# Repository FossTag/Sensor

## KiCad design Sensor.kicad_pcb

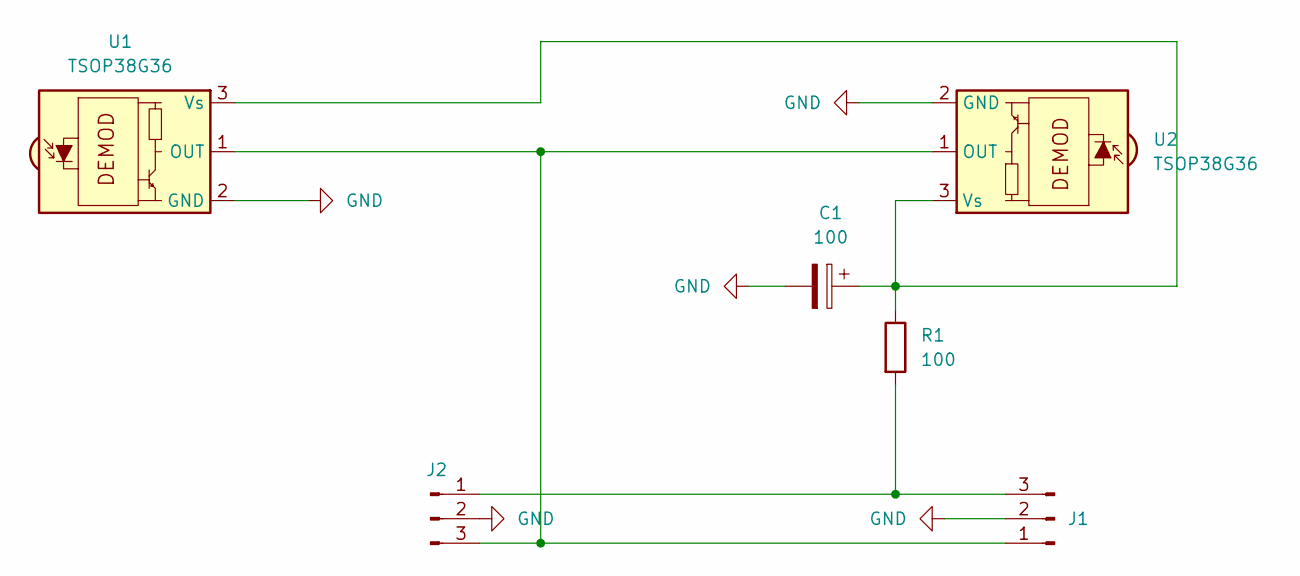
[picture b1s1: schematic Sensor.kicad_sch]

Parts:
C1: 100; CP_Radial_D5.0mm_P2.50mm
J1, J2: Conn_01x03_Male; SolderWire-0.1sqmm_1x03_P3.6mm_D0.4mm_OD1mm_Relief
R1: 100; R_Axial_DIN0204_L3.6mm_D1.6mm_P7.62mm_Horizontal
U1, U2: TSOP38G36; Vishay_MINICAST-3Pin

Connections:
GND: C1.2, J1.2, J2.2, U1.2 (GND), U2.2 (GND)
unnamed: C1.1, R1.1, U1.3 (Vs), U2.3 (Vs)
unnamed: J1.1, J2.3, U1.1 (OUT), U2.1 (OUT)
unnamed: J1.3, J2.1, R1.2

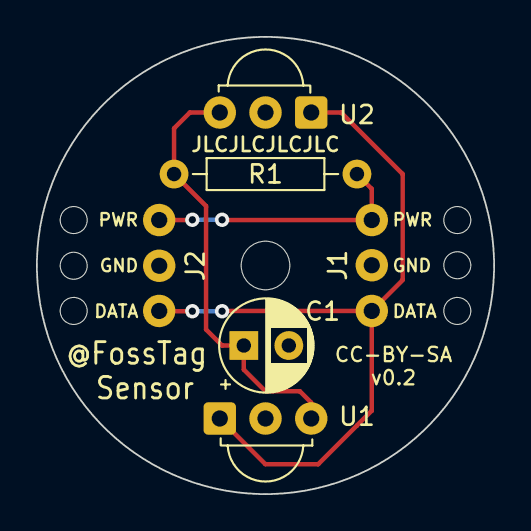
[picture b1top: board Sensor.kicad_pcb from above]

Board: 2 copper layers, 25.4 x 25.4 mm, 6 parts (0 on the bottom side), 4 nets.

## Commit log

2022-11-20 Initial v0.1 with a single connector.
    Future versions to include additional connectors to daisy chain
    multiples of these together.
2022-11-21 Second version with two connectors to allow daisychaining multiple modules together.

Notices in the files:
Sensor.kicad_pcb:
CC-BY-SA
